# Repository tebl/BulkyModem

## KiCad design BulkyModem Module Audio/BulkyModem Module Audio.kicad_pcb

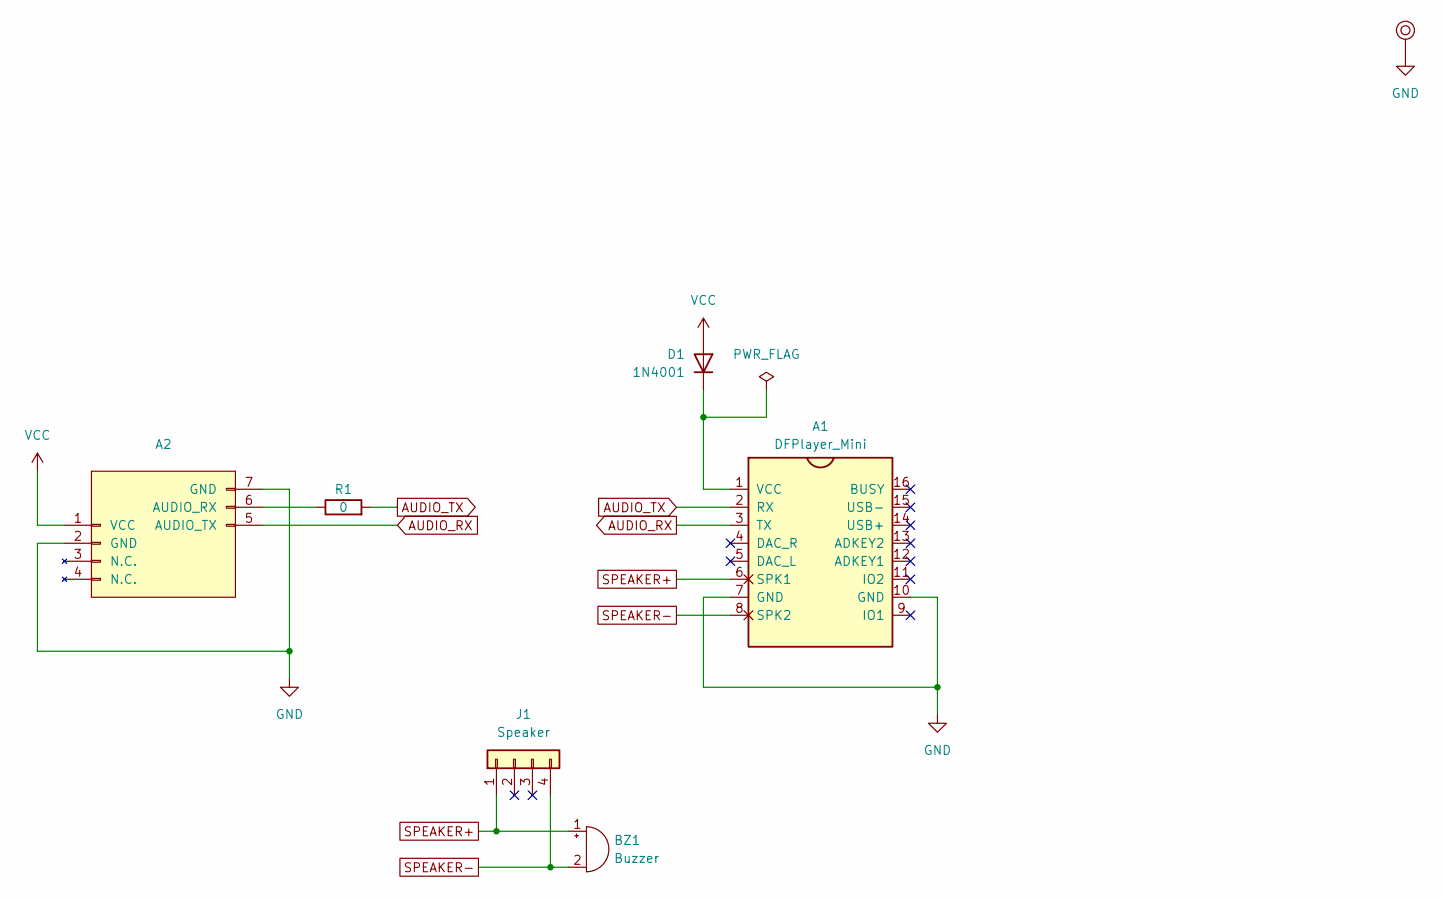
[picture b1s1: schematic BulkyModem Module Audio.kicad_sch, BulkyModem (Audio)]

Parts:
A1: DFPlayer_Mini
A2: AudioModule_Connector
BZ1: Buzzer; Buzzer_12x9.5RM7.6
D1: 1N4001; D_DO-41_SOD81_P10.16mm_Horizontal
J1: Speaker; PinHeader_1x04_P2.54mm_Horizontal
M1: Mounting_Pin; M3_pin
R1: 0; R_Axial_DIN0207_L6.3mm_D2.5mm_P10.16mm_Horizontal

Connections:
AUDIO_RX: A1.3 (TX), A2.5 (AUDIO_TX)
AUDIO_TX: A1.2 (RX), R1.2
GND: A1.7 (GND), A1.10 (GND), A2.2 (GND), A2.7 (GND), M1.1
unnamed: A1.1 (VCC), D1.1 (K)
unnamed: A2.6 (AUDIO_RX), R1.1
SPEAKER+: A1.6 (SPK1), BZ1.1 (+), J1.1
SPEAKER-: A1.8 (SPK2), BZ1.2 (-), J1.4
VCC: A2.1 (VCC), D1.2 (A)

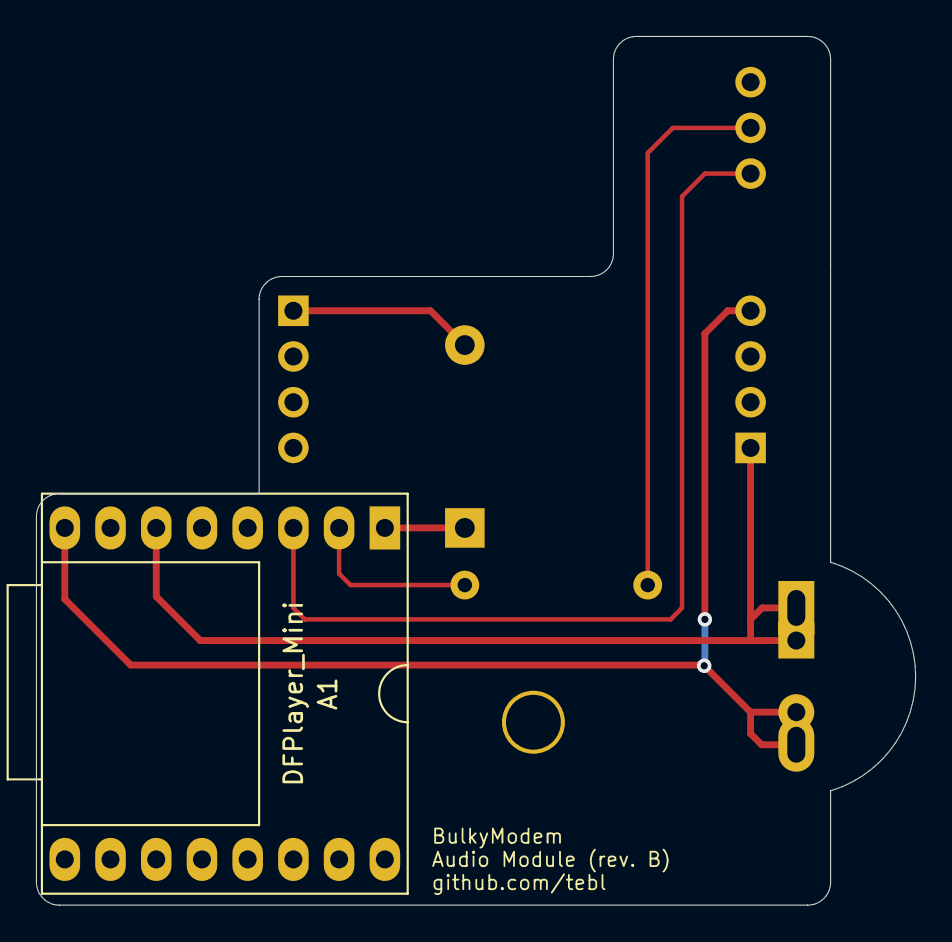
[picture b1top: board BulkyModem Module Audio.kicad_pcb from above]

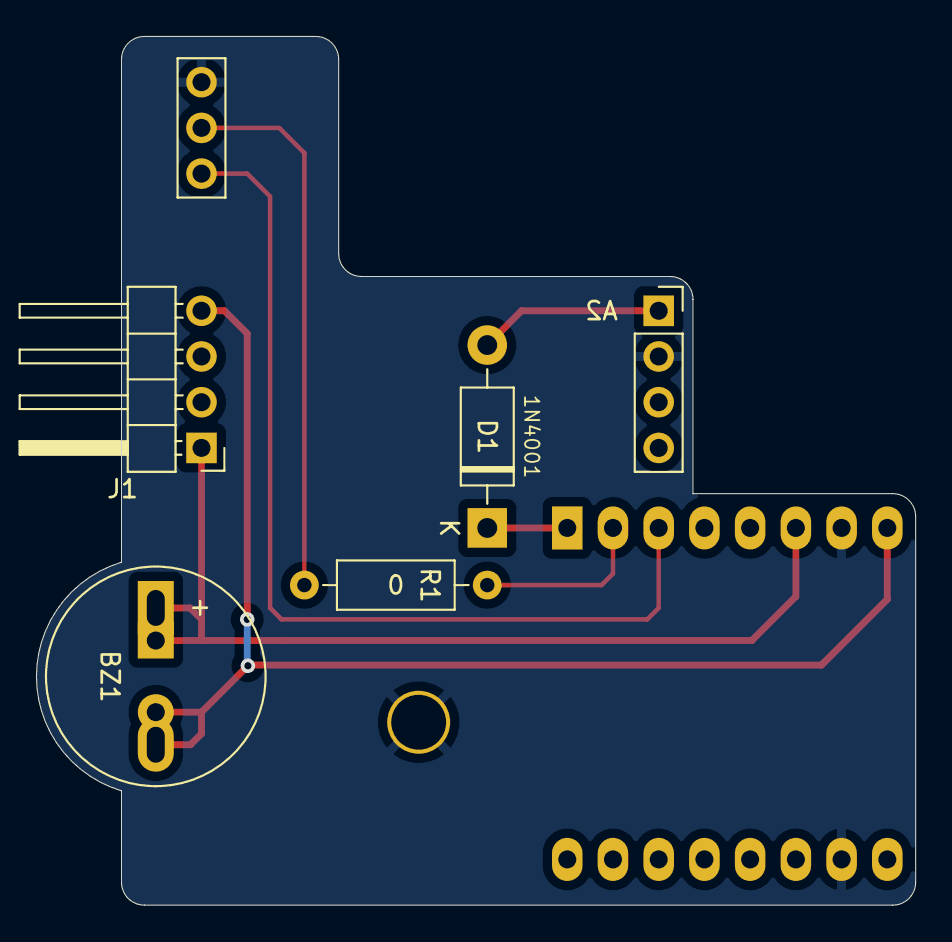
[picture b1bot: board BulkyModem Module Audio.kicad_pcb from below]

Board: 2 copper layers, 48.8 x 48.3 mm, 7 parts (4 on the bottom side), 8 nets.

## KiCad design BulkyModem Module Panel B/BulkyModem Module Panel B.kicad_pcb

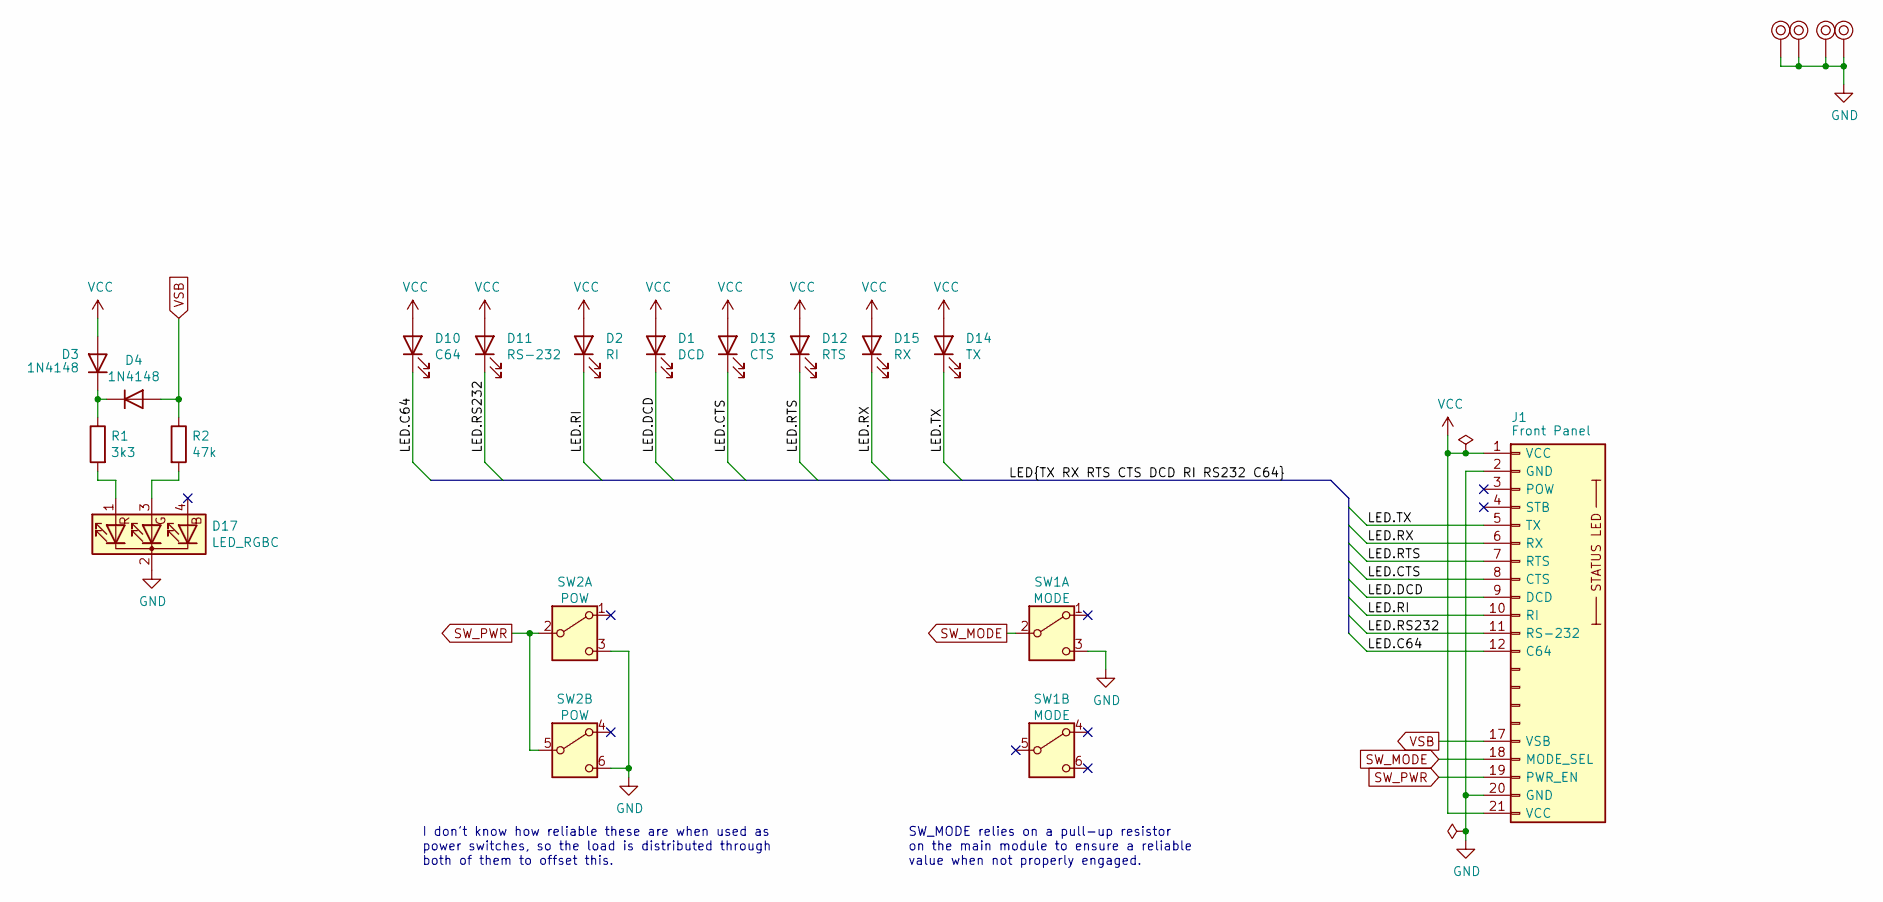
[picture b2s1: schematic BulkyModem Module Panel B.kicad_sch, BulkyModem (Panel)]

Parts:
D1: DCD; LED_D5.0mm
D2: RI; LED_D5.0mm
D3, D4: 1N4148; D_DO-35_SOD27_P7.62mm_Horizontal
D10: C64; LED_D5.0mm
D11: RS-232; LED_D5.0mm
D12: RTS; LED_D5.0mm
D13: CTS; LED_D5.0mm
D14: TX; LED_D5.0mm
D15: RX; LED_D5.0mm
D17: LED_RGBC; LED_D5.0mm-4_RGB_Wide_Pins
J1: Front Panel; PinHeader_1x21_P2.54mm_Horizontal
M1, M2, M3, M4: Mounting_Pin; M3_pin
R1: 3k3; R_Axial_DIN0207_L6.3mm_D2.5mm_P10.16mm_Horizontal
R2: 47k; R_Axial_DIN0207_L6.3mm_D2.5mm_P10.16mm_Horizontal
SW1: MODE; dpdt_switch_black
SW2: POW; dpdt_switch_black

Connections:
/LED.C64: D10.1 (K), J1.12 (C64)
/LED.CTS: D13.1 (K), J1.8 (CTS)
/LED.DCD: D1.1 (K), J1.9 (DCD)
/LED.RI: D2.1 (K), J1.10 (RI)
/LED.RS232: D11.1 (K), J1.11 (RS-232)
/LED.RTS: D12.1 (K), J1.7 (RTS)
/LED.RX: D15.1 (K), J1.6 (RX)
/LED.TX: D14.1 (K), J1.5 (TX)
GND: D17.2 (K), J1.2 (GND), J1.20 (GND), M1.1, M2.1, M3.1, M4.1, SW1.3 (C), SW2.3 (C), SW2.6 (C)
unnamed: D3.1 (K), D4.1 (K), R1.1
unnamed: D17.3 (GA), R2.2
unnamed: D17.1 (RA), R1.2
SW_MODE: J1.18 (MODE_SEL), SW1.2 (B)
SW_PWR: J1.19 (PWR_EN), SW2.2 (B), SW2.5 (B)
VCC: D1.2 (A), D2.2 (A), D3.2 (A), D10.2 (A), D11.2 (A), D12.2 (A), D13.2 (A), D14.2 (A), D15.2 (A), J1.1 (VCC), J1.21 (VCC)
VSB: D4.2 (A), J1.17 (VSB), R2.1

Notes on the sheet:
SW_MODE relies on a pull-up resistor on the main module to ensure a reliable value when not properly engaged.
I don't know how reliable these are when used as power switches, so the load is distributed through both of them to offset this.

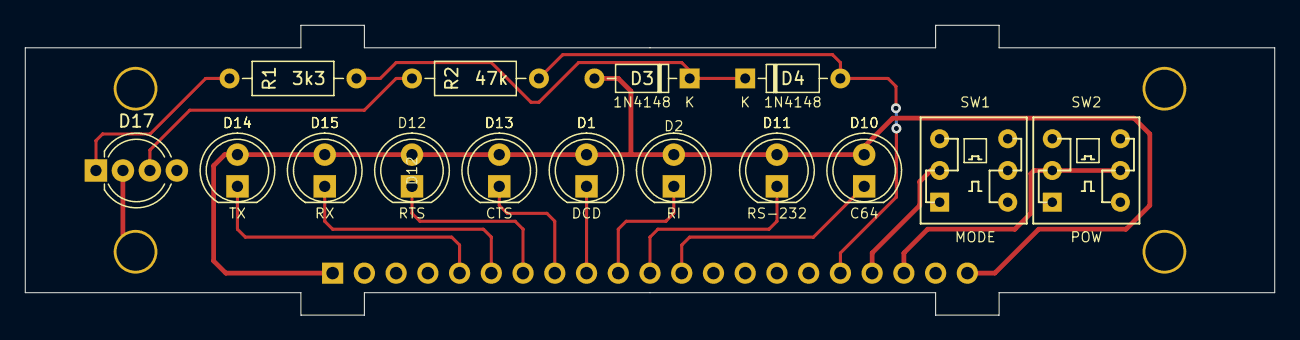
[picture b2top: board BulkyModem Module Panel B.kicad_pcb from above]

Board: 2 copper layers, 100.0 x 23.2 mm, 20 parts (1 on the bottom side), 16 nets.

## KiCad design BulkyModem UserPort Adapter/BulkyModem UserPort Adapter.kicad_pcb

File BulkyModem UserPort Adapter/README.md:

# BulkyModem C64/128 UserPort Adapter
This is an adapter for connecting up the *BulkyModem*, alternatively the functionally similar *BulkyModem-32*, up to everyone's favorite 8-bit system that's not the NES. Commodore 64! The answer is Commodore 64! Got that? Yes, it's also compatible with the Commodore 128 if that's what you were thinking about. It currently looks like this:

You plug the adapter into the *User Port* on your computer, then it hooks up to your *BulkyModem* using commonly available *2x8 pin IDC cable* that's regularly sold on the regular sites. As for why you need an adapter, it started out as a straight up adapter with no active components on it though I soon discovered that you generally don't want independently powered devices connected in this way. It'll work like it should, but the second you power off either of the devices, then the other will start backfeeding power to it through the data lines. Ouch! So I did the a 70s fix by adding line buffers, and then only enabling them once both sides have been properly powered up.

**NB!** Note, however, that with a Commodore 128 you will not be able to utilize UP9600-wiring for speeds above 1200 baud. That's a limitation of the machine in combination with this specific communication method, and not the adapter itself. See [Getting started](https://github.com/tebl/BulkyModem/blob/main/documentation/getting_started_c64.md#21-up9600) guide for the Commodore 64/128, in particular, for more information. 

- [1> Building the adapter](#1-building-the-adapter)
  - [1.1> Soldering it together](#11-soldering-it-together)
  - [1.2> Testing it out](#12-testing-it-out)
- [2> Schematic](#2-schematic)
- [3> BOM](#3-bom)

# 1> Building the adapter
Building an adapter such as this assumes you have at least minor experience soldering things together, but it is recommended that you at the very least have access to a soldering station with adjustable temperature. If it's legally available where you live, consider using 60/40 rosin core solder as the lead-free alternatives tends to be a bit harder to work with.

Now that you've arrived at *concepts of a plan* for what you want to build, we can get started on one of the more expensive steps in any build process - shopping! For reference, the most expensive step is probably setting your desk and/or house on fire so don't drink and solder. Anyway, when ready to continue with the whole shopping thing that you've heard so much about - head on over to the [BOM](#3-bom)-section. There you'll find *mostly* accurate information on the kind of components that you'll need.

While I would have liked to give you specific part numbers for "reputable" electronic part suppliers, I can't afford to shop there personally. So what I do, is to make due with what I can find on sites such as eBay, AliExpress or any other future site that will inevitably seem to sell the same, and quite possibly identical set of cheap Chinese components. It keeps cost to a minimum, but the downside is that I can't link to a part directly and expect it to stay listed tomorrow. For that reason you'll need to consider their descriptions as mere *suggested search terms* and not *part numbers* in any accurate sense of the definition.

## 1.1> Soldering it together
Soldering the device together should be a fairly straight-forward affair, just take your time and work your way through the described process before actually attempting to do so. There are some important components that absolutely need to be installed in their correct orientation, and from experience I can tell you that it is significantly easier to do it right in the first place, than it is to try and desolder something before trying again.

I usually recommend starting the process by having a good look at the PCBs, try to figure out where all of the listed components should go and in which orientation they go in. I will usually try to install components in the order of their physical size, meaning that you'll have an easier time in order to keep everything from looking somewhat *wonky*. Anyway, this is ultimately your board, your build and you want it perfect, don't you? If you said no, then go sit in the corner because I worked hard on creating this. Mainly for myself, but it's also here for whoever wants to build one later.

First step though, is to install resistors. While most of them should be installed with the values as specified, the ones marked 2k2 (2200) Ohm may need some adjustment based on the type of LEDs that you'll be installing later. If you have a modern clear LED you'll want a higher value, if you have the cheaper dyed ones then you want something lower. There are [online calculators](https://ledcalculator.net/#p=3&v=1.8&c=20&n=1&o=w) that will tell you what you need, or you can *roll that dice* and hope for a comfortable result.

The next step is diodes, and there are a couple of types that have been installed at this point. The first type to deal with is the two *1N5819 Schottky* diodes at the far right, these have a black body and a silver stripe that needs to be matched up in the orientation as indicated by the white band on the illustration (these "point" towards each other).

The others are *1N4731A Zener* (alternatively *1N4730A*) diodes, these work a bit different from how we mortal Arduino-tinkerers think of diodes - they were defined to "break" down beyond a certain voltage. Not *"break down"* as in broken, it means that they will start conducting in the other direction above it. This effect is used by the circuit so that we can reliably detect the presence of power from the *BulkyModem* as well as ensuring that the Commodore 64/128 is sufficiently powered on. Is that a good way of doing things? I don't know, it's my first time trying to use the component in a circuit.

Sockets should be installed for the single IC needed to build the adapter. While you could possibly manage without using a socket, they're cheap and you could probably afford not to be quite as cheap. To install I usually solder opposing corners into place, then reheat and push flush against the board before soldering the remaining pins. Note the indent that would indicate pin 1, the silkscreen on your PCB should have something similar on it that you will need to match it up to.

As for my next component of choice, I went with the 100nF capacitor next to the IC. While I did add some provision for an electrolytic at *C2*, in the end I chose not to install it. As for the LEDs that we've in part discussed at some point in the past, mostly in relation to the resistors limiting their brightness. As for their installation, one of their legs will be longer than the other - and that's the one to put into the round pad. I know that the function of each leg implies a more exact name for them, I'm not going to put something I can't even remember myself. Cathode? Anode? One of those two. Just pick the longer one.

Two transistors are needed, both are *2N3904 NPN transistors*. The kind I'm using has straight legs. but my PCB takes the wider kind with bent legs because those are easier to install. I could try and buy those from somewhere that sells them, or I could keep buying the significantly cheaper ones and just bend the outer legs slightly outwards before showing them into place. They tend to rotate slightly, but should work nonetheless. What you do, however, need to make sure is that they go in the right way. For that you need to observe that it has a flat side with the label printed on it, that needs to be matched with the flat side on the PCB. Put them in the wrong around for a tiny one-time-use smoke machine that will never do any of the things that you want them to.

I've gone ahead and added the straight pin headers for the *UP9600-enable* jumpers. Use some blu-tac to avoid burning your fingers, but if you don't have some around you *could* try to hold onto the pin you're not soldering and get that in straight. The latter method is mostly guaranteed to burn your fingers, but at least you were "sufficiently" warned. The IDC-socket at the top could be substituted by standard pin headers if you need to, but I like using them in order to avoid accidentally plugging in the cable the wrong way around.

The next one is a standard 805 card edge-connector, they come in a couple of variants - one that has a thin pin intended for inserting into a PCB, the other has wider pins suitable for soldering onto wires. Both will work though I prefer the latter as the pins seem somewhat stronger. What we need to do in order to install it, however, is to not start soldering things right away - instead we need to break out that secret stash of M3 screws and nuts that you've been hiding. Preferably I'd tell you to use those made out of nylon as you can easily cut a screw down to size, at least without digging out a hacksaw and quite possibly look in the garage for a table vice.

Anyway, what we need to do is to cut two screws down to size so that they fit through the blue connector  without bottoming out in the cutouts found on your PCB. Said cutout should fit the flat edge of a nylon M3-nut, so just put one in there and start screwing things up. Somewhat tightly as it is nylon after all, try again if that's what you've just done.

With the screws mostly holding the connector into place, the pins themselves will float somewhat above the PCB-surface on both sides. What I like to do at this point, is to take a small flat-edged screwdriver and press it down on the middle of the pin so that it bends down and the end of it *mostly* touches the solder pads. I say "mostly" because it's never perfectly flat, it's just the best I can manage. Solder one of the pins, check against the alignment of the same on the other side of the PCB to see if you need to adjust things slightly. When happy with your choice of hobbies, do the opposing edge in the same manner before soldering all the remaining pins on both sides.

The final step is just to insert the single IC, it has an indent on it shat should match the one found on the socket we've already installed at a previous point in this guide. As for the jumpers I've just put them on there so that I don't loose them, in this position they are only sitting on a single pin.

## 1.2> Testing it out
The jumpers mentioned earlier are for using *UP9600*-mode on a Commodore 64 with software that explicitly supports it, some even require that you configure this mode without it connected at the time. As for on a Commodore 128 this mode is not supported at all, so should either remove them entirely or leave them in the horizontal position as shown earlier.  For more information about UP9600, see [Getting started](https://github.com/tebl/BulkyModem/blob/main/documentation/getting_started_c64.md#21-up9600) guide for the Commodore 64/128.

As for testing out the adapter, I advise that you first test it with only the *BulkyModem*, alternatively *BulkyModem-32*, connected to it. If something is going to blow up, better that it do so when not connected to vintage and quite possibly precious hardware. The LED marked *PWR* should light up, but without the Commodore 64 present and powered up - the *EN* LED should not turn on.

Plugging it into a Commodore 64/128 may take some considerable force, the connector is brand new and may have been 40 years since you last encountered a new one. With the cable and everything in place you should not be able to comfortably insert it upside down, but in case you need me to paint you a picture - there's one above. If you find it hard to remove again later, don't pull on the components themselves. Instead you should either grab the sides firmly, or put a loop of cable into the holes on it - and pull on that.

**NB!** Never plug or unplug anything with power running to it, even if it is just on the other side of the cable. Vintage hardware may have survived things quite a lot of things 40 years ago, but they were new back then - now they're not.

# 2> Schematic
The supplied KiCad files should be sufficient as both a schematic and as a  starting point for ordering PCBs. Most if not all fabrication companies will expect Gerber-files, these are generated from KiCAD though you will be able to bypass this step by using PCBway shared projects. As for the schematic, one has been provided for you in [PDF-format](https://github.com/tebl/BulkyModem/tree/main/documentation/schematic) - an important source of information when things inevitably fail to work as advertised.

# 3> BOM
Most parts should be easy to get a hold of from your favorite local electronic component shop, but given that I don't have access to such shops where I live so everything was based on whatever I could get cheapest from eBay/AliExpress (free shipping, but plan on waiting 3-4 weeks for delivery).

| Reference             | Item                                                                    | Count | Order  |
| --------------------- | ----------------------------------------------------------------------- | ----- | ------ |
| Panel PCB             | Fabricate using Gerber files                                            |     1 | [PCBWay](https://www.pcbway.com/project/shareproject/BulkyModem_Commodore_64_128_UserPort_Adapter_a84c7ef6.html)
| C1                    | 100nF capacitor (5mm pin spacing, or 1uF electrolytic (2mm pin spacing) |     1 |
| C2                    | Not needed.                                                             |     0 |
| D1,D4                 | 1N4731A Zener diode (DO-41)                                             |     2 |
| D2,D3 *1              | 3mm LED                                                                 |     1 |
| D5,D6			        | 1N5819 Schottky diode (DO-41)                                           |     2 |
| J1                    | 2x12 pin, 3.96mm 805 series card edge connector                         |     1 |
| J3                    | 2x8 pin, 2.54mm IDC male box header connector                           |     1 |
| JP1,JP2               | 1x2 pin, 2.54mm straight pin header (with jumper cap)                   |     2 |
| Q1,Q2                 | 2N3904 NPN transistor (TO-92)                                           |     2 |
| R1,R4,R6              | 10k ohm resistor                                                        |     3 |
| R2,R5                 | 1k ohm resistor                                                         |     2 |
| R3,R7 *1              | 2k2 (2200) ohm resistor                                                 |     2 |
| U1                    | 74HCT244 (DIP-20)                                                       |     1 |
| Mounting *2           | M3x15mm nylon screws (or longer, cut to size)                           |     2 |
| Mounting *2           | M3 nylon nuts                                                           |     2 |

1) I highly recommend using frosted LEDs, but if you can only find clear ones then you could always frost them a bit yourself using sandpaper or some sort of polishing tool. Do note that some resistors need to be adjusted based on type of LED used. For a modern LED the suggested value may work, but you may need to adjust for the colour. For anything ancient, or extremely cheap, you may need a lower value. 
2) These are often sold in kits, but you usually also find bags of each on the usual sites. Nylon is strong enough for my purposes while easy enough to cut down to a suitable size.

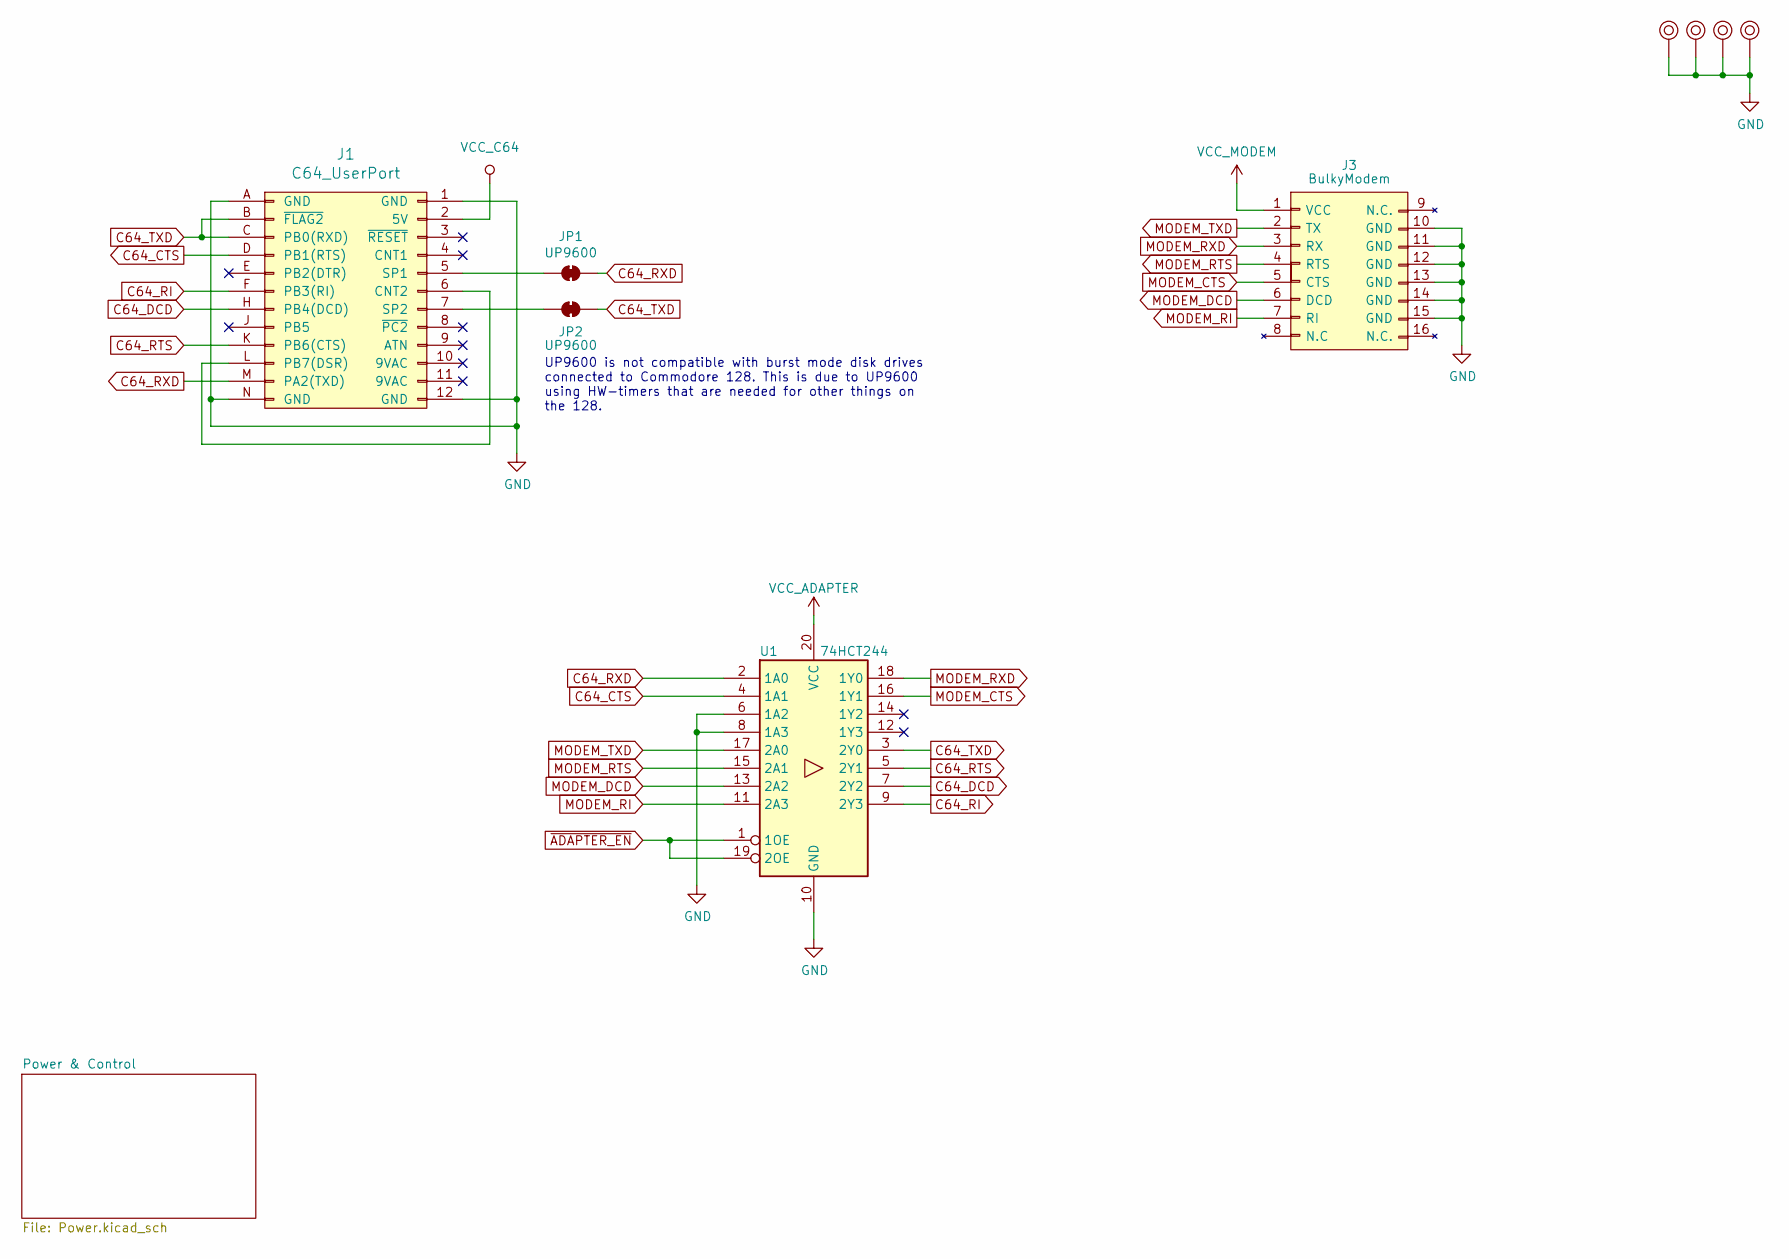
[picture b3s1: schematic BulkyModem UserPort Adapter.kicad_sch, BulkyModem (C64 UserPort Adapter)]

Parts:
J1: C64_UserPort; C64_User-Port
J3: BulkyModem; UserPort_Adapter_IDC
JP1, JP2: UP9600; PinHeader_1x02_P2.54mm_Vertical
M1, M2, M3, M4: Mounting; M3_pin
U1: 74HCT244; DIP-20_W7.62mm_Socket_LongPads

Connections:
C64_CTS: J1.D (PB1(RTS)), U1.4 (1A1)
C64_DCD: J1.H (PB4(DCD)), U1.7 (2Y2)
C64_RI: J1.F (PB3(RI)), U1.9 (2Y3)
C64_RTS: J1.K (PB6(CTS)), U1.5 (2Y1)
C64_RXD: J1.M (PA2(TXD)), JP1.2 (B), U1.2 (1A0)
C64_TXD: J1.B (~FLAG2), J1.C (PB0(RXD)), JP2.2 (B), U1.3 (2Y0)
GND: J1.1 (GND), J1.12 (GND), J1.A (GND), J1.N (GND), J3.10 (GND), J3.11 (GND), J3.12 (GND), J3.13 (GND), J3.14 (GND), J3.15 (GND), M1.1, M2.1, M3.1, M4.1, U1.6 (1A2), U1.8 (1A3), U1.10 (GND); also elsewhere on the board
MODEM_CTS: J3.5 (CTS), U1.16 (1Y1)
MODEM_DCD: J3.6 (DCD), U1.13 (2A2)
MODEM_RI: J3.7 (RI), U1.11 (2A3)
MODEM_RTS: J3.4 (RTS), U1.15 (2A1)
MODEM_RXD: J3.3 (RX), U1.18 (1Y0)
MODEM_TXD: J3.2 (TX), U1.17 (2A0)
unnamed: J1.6 (CNT2), J1.L (PB7(DSR))
unnamed: J1.5 (SP1), JP1.1 (A)
unnamed: J1.7 (SP2), JP2.1 (A)
VCC_ADAPTER: U1.20 (VCC); also elsewhere on the board
VCC_C64: J1.2 (5V); also elsewhere on the board
VCC_MODEM: J3.1 (VCC); also elsewhere on the board
~ADAPTER_EN: U1.1 (1OE), U1.19 (2OE); also elsewhere on the board

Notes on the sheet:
UP9600 is not compatible with burst mode disk drives connected to Commodore 128. This is due to UP9600 using HW-timers that are needed for other things on the 128.

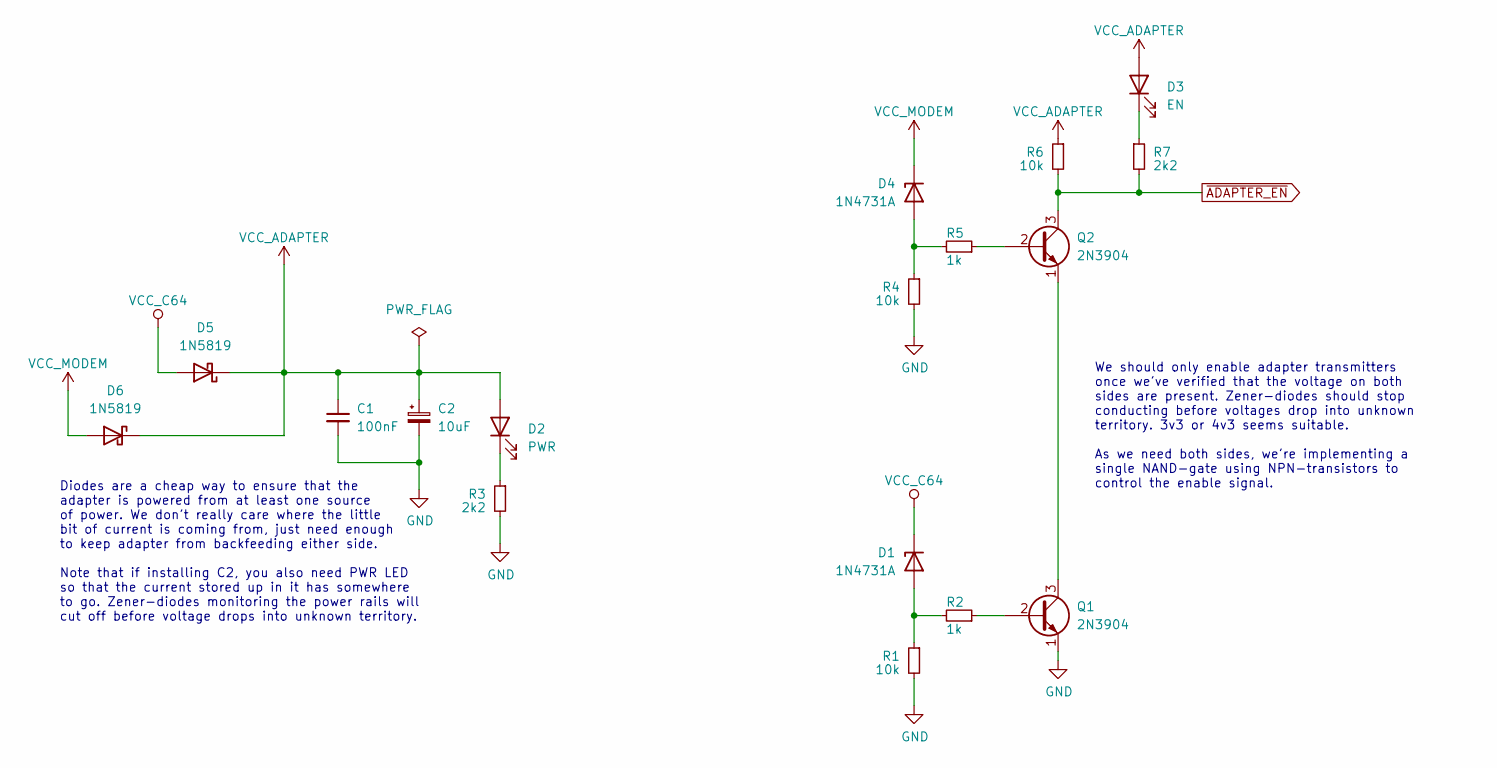
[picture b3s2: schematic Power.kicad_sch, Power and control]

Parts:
C1: 100nF; C_Disc_D4.7mm_W2.5mm_P5.00mm
C2: 10uF; CP_Radial_D4.0mm_P2.00mm
D1, D4: 1N4731A; D_DO-41_SOD81_P10.16mm_Horizontal
D2: PWR; LED_D3.0mm
D3: EN; LED_D3.0mm
D5, D6: 1N5819; D_DO-41_SOD81_P10.16mm_Horizontal
Q1, Q2: 2N3904; TO-92_Inline_Wide
R1, R4, R6: 10k; R_Axial_DIN0207_L6.3mm_D2.5mm_P10.16mm_Horizontal
R2, R5: 1k; R_Axial_DIN0207_L6.3mm_D2.5mm_P10.16mm_Horizontal
R3, R7: 2k2; R_Axial_DIN0207_L6.3mm_D2.5mm_P10.16mm_Horizontal

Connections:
GND: C1.2, C2.2, Q1.1 (E), R1.2, R3.2, R4.2; also elsewhere on the board
unnamed: D1.2 (A), R1.1, R2.2
unnamed: D2.1 (K), R3.1
unnamed: D3.1 (K), R7.1
unnamed: D4.2 (A), R4.1, R5.2
unnamed: Q1.2 (B), R2.1
unnamed: Q1.3 (C), Q2.1 (E)
unnamed: Q2.2 (B), R5.1
VCC_ADAPTER: C1.1, C2.1, D2.2 (A), D3.2 (A), D5.1 (K), D6.1 (K), R6.1; also elsewhere on the board
VCC_C64: D1.1 (K), D5.2 (A); also elsewhere on the board
VCC_MODEM: D4.1 (K), D6.2 (A); also elsewhere on the board
~ADAPTER_EN: Q2.3 (C), R6.2, R7.2; also elsewhere on the board

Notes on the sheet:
We should only enable adapter transmitters once we've verified that the voltage on both sides are present. Zener-diodes should stop conducting before voltages drop into unknown territory. 3v3 or 4v3 seems suitable. As we need both sides, we're implementing a single NAND-gate using NPN-transistors t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
Diodes are a cheap way to ensure that the adapter is powered from at least one source of power. We don't really care where the little bit of current is coming from, just need enough to keep adapter from backfeeding either side. Note that if installing C2, you also need PWR LED so that the current s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

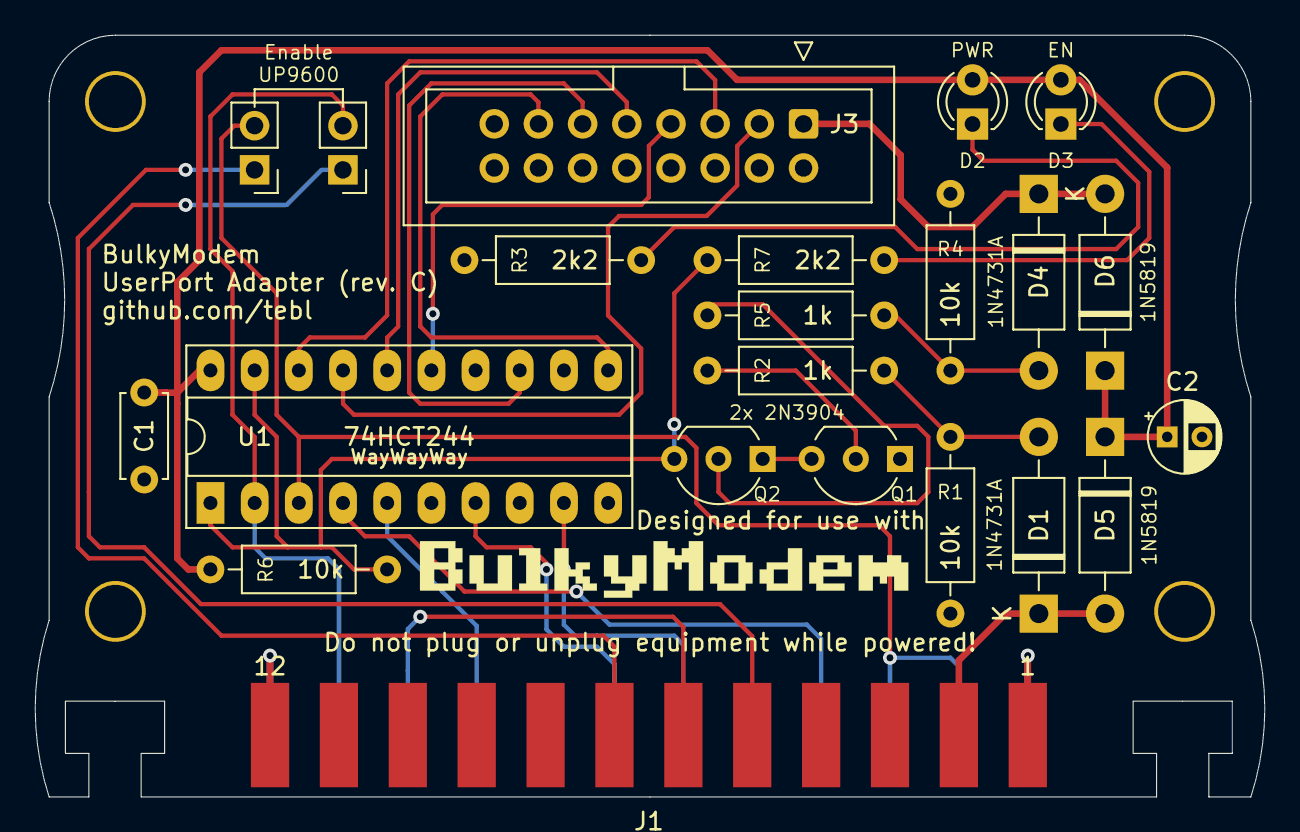
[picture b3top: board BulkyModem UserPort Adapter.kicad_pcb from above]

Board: 2 copper layers, 70.7 x 43.8 mm, 26 parts (0 on the bottom side), 27 nets.

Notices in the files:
BulkyModem UserPort Adapter/BulkyModem UserPort Adapter.kicad_pcb:
Licensed under CERN OHL v1.2
